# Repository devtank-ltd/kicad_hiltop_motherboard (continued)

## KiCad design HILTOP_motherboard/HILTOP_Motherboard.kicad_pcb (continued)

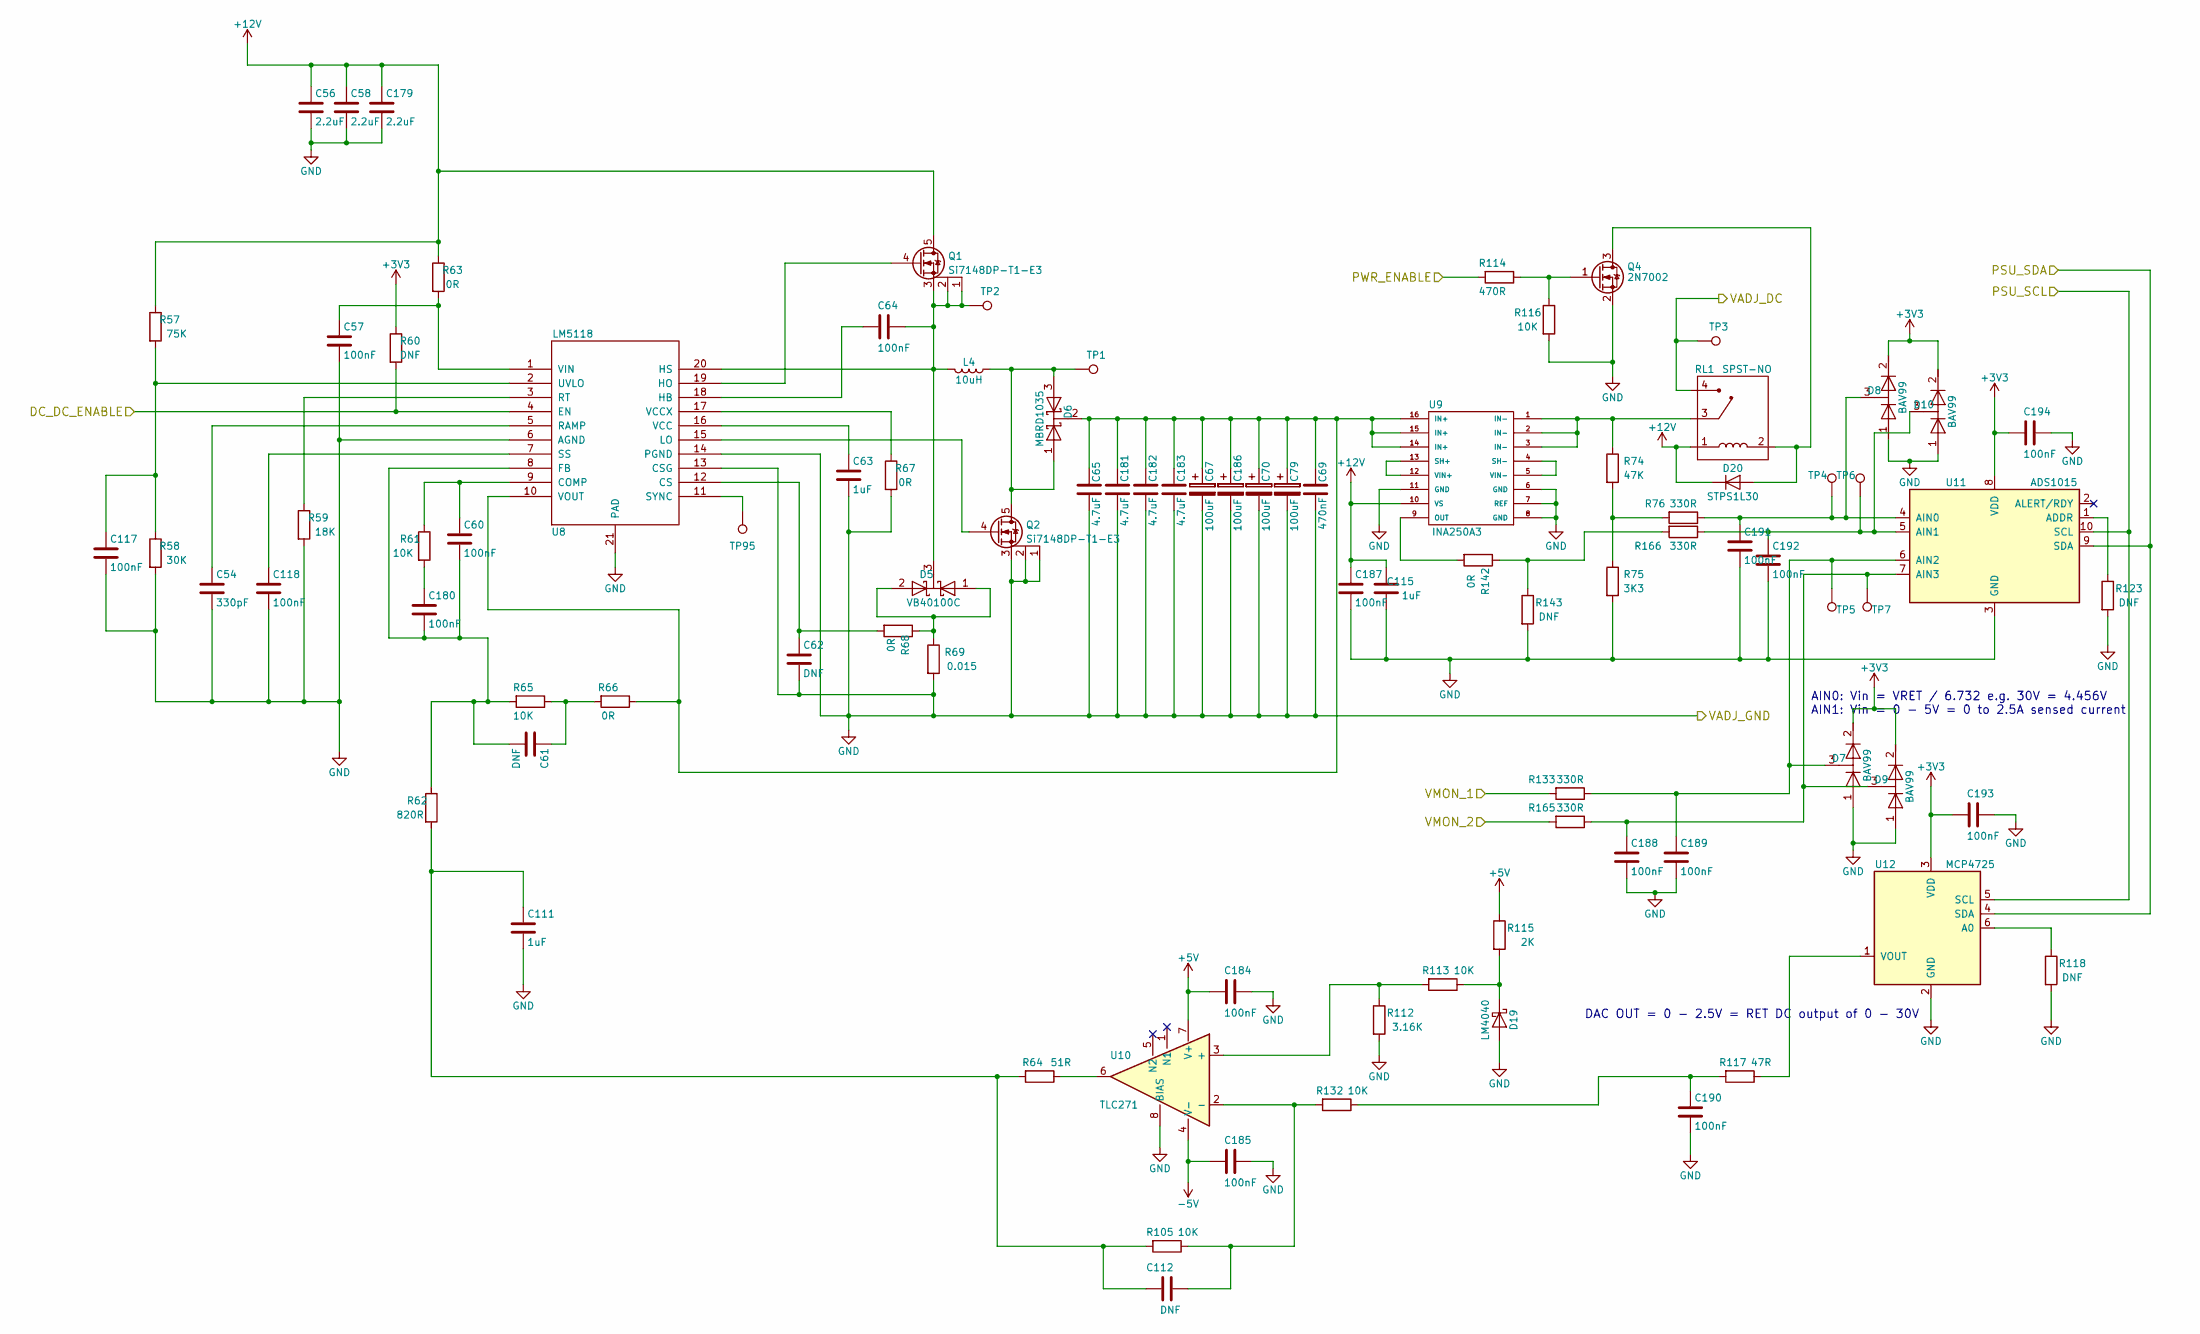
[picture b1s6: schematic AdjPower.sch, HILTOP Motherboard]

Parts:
C54: 330pF; C_0402_1005Metric
C56, C58, C179: 2.2uF; C_1206_3216Metric
C57, C60, C64, C117, C118, C180, C184, C185, C187, C188, C189, C190, C191, C192, C193, C194: 100nF; C_0603_1608Metric
C61, C62, C112: DNF; C_0603_1608Metric
C63, C111, C115: 1uF; C_0805_2012Metric
C65, C181, C182, C183: 4.7uF; C_1210_3225Metric
C67, C70, C79, C186: 100uF; CP_Elec_6.3x7.7
C69: 470nF; C_0805_2012Metric
D5: VB40100C; TO-263AB
D6: MBRD1035; DPAK
D7, D8, D9, D10: BAV99; SOT-23
D19: LM4040; SOT-23
D20: STPS1L30; D_SMB
L4: 10uH; Inductor_Coilcraft_SER2800
Q1, Q2: Si7148DP-T1-E3; PowerPAK_SO-8
Q4: 2N7002; SOT-23
R57: 75K; R_0603_1608Metric
R58: 30K; R_0603_1608Metric
R59: 18K; R_0603_1608Metric
R60, R118, R123, R143: DNF; R_0603_1608Metric
R61, R65, R105, R113, R116, R132: 10K; R_0603_1608Metric
R62: 820R; R_0603_1608Metric
R63: 0R; R_1206_3216Metric
R64: 51R; R_0603_1608Metric
R66, R67, R68, R142: 0R; R_0603_1608Metric
R69: 0.015; RL7520W_3008
R74: 47K; R_0603_1608Metric
R75: 3K3; R_0603_1608Metric
R76, R133, R165, R166: 330R; R_0603_1608Metric
R112: 3.16K; R_0603_1608Metric
R114: 470R; R_0603_1608Metric
R115: 2K; R_0603_1608Metric
R117: 47R; R_0603_1608Metric
RL1: SPST-NO; Relay_SPST_TE_PCH
TP1, TP2, TP3, TP4, TP5, TP6, TP7, TP95: TP; TestPoint_THTPad_D1.0mm_Drill0.5mm
U8: LM5118; HTSSOP-20-1EP_4.4x6.5mm_P0.65mm_ThermalPad
U9: INA250A3; TSSOP-16_4.4x5mm_P0.65mm
U10: TLC271; SOIC-8_3.9x4.9mm_P1.27mm
U11: ADS1015; TSSOP-10_3x3mm_P0.5mm
U12: MCP4725; SOT-23-6

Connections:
+3V3: C193.2, C194.2, D7.2 (K), D8.2 (K), D9.2 (K), D10.2 (K), R60.1, U11.8 (VDD), U12.3 (VDD); also elsewhere on the board
+12V: C56.1, C58.1, C115.2, C179.1, C187.1, D20.1 (K), Q1.5 (D), R57.1, R63.1, RL1.1, U9.10 (VS); also elsewhere on the board
-5V: C185.2, U10.4 (V-); also elsewhere on the board
/AdjPower/VADJ_DC: RL1.4, TP3.1; also elsewhere on the board
/AdjPower/VMON_1: R133.2; also elsewhere on the board
/AdjPower/VMON_2: R165.2; also elsewhere on the board
/DC_DC_ENABLE: R60.2, U8.4 (EN); also elsewhere on the board
/DC_OUT_ENABLE: R114.2; also elsewhere on the board
/I2C1_SCL: U11.10 (SCL), U12.5 (SCL); also elsewhere on the board
/I2C1_SDA: U11.9 (SDA), U12.4 (SDA); also elsewhere on the board
GND: C54.2, C56.2, C57.2, C58.2, C62.2, C63.2, C65.1, C67.2, C69.1, C70.2, C79.2, C111.2, C115.1, C117.2, C118.2, C179.2, C181.1, C182.1, C183.1, C184.1, C185.1, C186.2, C187.2, C188.2, C189.2, C190.2, C191.2, C192.2, C193.1, C194.1, D7.1 (A), D8.1 (A), D9.1 (A), D10.1 (A), D19.2 (A), Q2.1, Q2.2, Q2.3 (S), Q4.2 (S), R58.2, R59.2, R67.2, R69.2, R75.2, R112.2, R116.2, R118.2, R123.2, R143.2, U8.6 (AGND), U8.13 (CSG), U8.14 (PGND), U8.21 (PAD), U9.6 (GND), U9.7 (REF), U9.8 (GND), U9.11 (GND), U10.8 (BIAS), U11.3 (GND), U12.2 (GND); also elsewhere on the board
unnamed: C54.1, U8.5 (RAMP)
unnamed: C57.1, R63.2, U8.1 (VIN)
unnamed: C60.1, R61.1, U8.9 (COMP)
unnamed: C61.1, R65.1, R66.2
unnamed: C62.1, R68.2, U8.12 (CS)
unnamed: C63.1, U8.16 (VCC)
unnamed: C64.1, D5.3 (K), L4.2, Q1.1, Q1.2, Q1.3 (S), TP2.1, U8.20 (HS)
unnamed: C64.2, U8.18 (HB)
unnamed: C111.1, C112.1, R62.2, R64.2, R105.2
unnamed: C112.2, R105.1, R132.2, U10.2 (-)
unnamed: C117.1, R57.2, R58.1, U8.2 (UVLO)
unnamed: C118.1, U8.7 (SS)
unnamed: C180.1, R61.2
unnamed: C60.2, C61.2, C180.2, R62.1, R65.2, U8.8 (FB)
unnamed: C65.2, C67.1, C69.2, C70.1, C79.1, C181.2, C182.2, C183.2, C186.1, D6.2 (K), R66.1, U8.10 (VOUT), U9.14 (IN+), U9.15 (IN+), U9.16 (IN+)
unnamed: C188.1, D9.3 (common), R165.1, TP7.1, U11.7 (AIN3)
unnamed: C189.1, D7.3 (common), R133.1, TP5.1, U11.6 (AIN2)
unnamed: C190.1, R117.2, R132.1
unnamed: C191.1, D8.3 (common), R76.1, TP4.1, U11.4 (AIN0)
unnamed: C192.1, D10.3 (common), R166.1, TP6.1, U11.5 (AIN1)
unnamed: D5.1 (A), D5.2 (A), R68.1, R69.1
unnamed: D6.1 (A), D6.3 (A), L4.1, Q2.5 (D), TP1.1
unnamed: D19.1 (K), R113.1, R115.2
unnamed: D20.2 (A), Q4.3 (D), RL1.2
unnamed: Q1.4 (G), U8.19 (HO)
unnamed: Q2.4 (G), U8.15 (LO)
unnamed: Q4.1 (G), R114.1, R116.1
unnamed: R59.1, U8.3 (RT)
unnamed: R64.1, U10.6
unnamed: R67.1, U8.17 (VCCX)
unnamed: R74.1, RL1.3, U9.1 (IN-), U9.2 (IN-), U9.3 (IN-)
unnamed: R74.2, R75.1, R76.2
unnamed: R112.1, R113.2, U10.3 (+)
unnamed: R117.1, U12.1 (VOUT)
unnamed: R118.1, U12.6 (A0)
unnamed: R123.1, U11.1 (ADDR)
unnamed: R142.1, R143.1, R166.2
unnamed: R142.2, U9.9 (OUT)
unnamed: TP95.1, U8.11 (SYNC)
unnamed: U9.4 (SH-), U9.5 (VIN-)
unnamed: U9.12 (VIN+), U9.13 (SH+)

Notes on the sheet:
AIN0: Vin = VRET / 6.732 e.g. 30V = 4.456V AIN1: Vin = 0 - 5V = 0 to 2.5A sensed current
DAC OUT = 0 - 2.5V = RET DC output of 0 - 30V

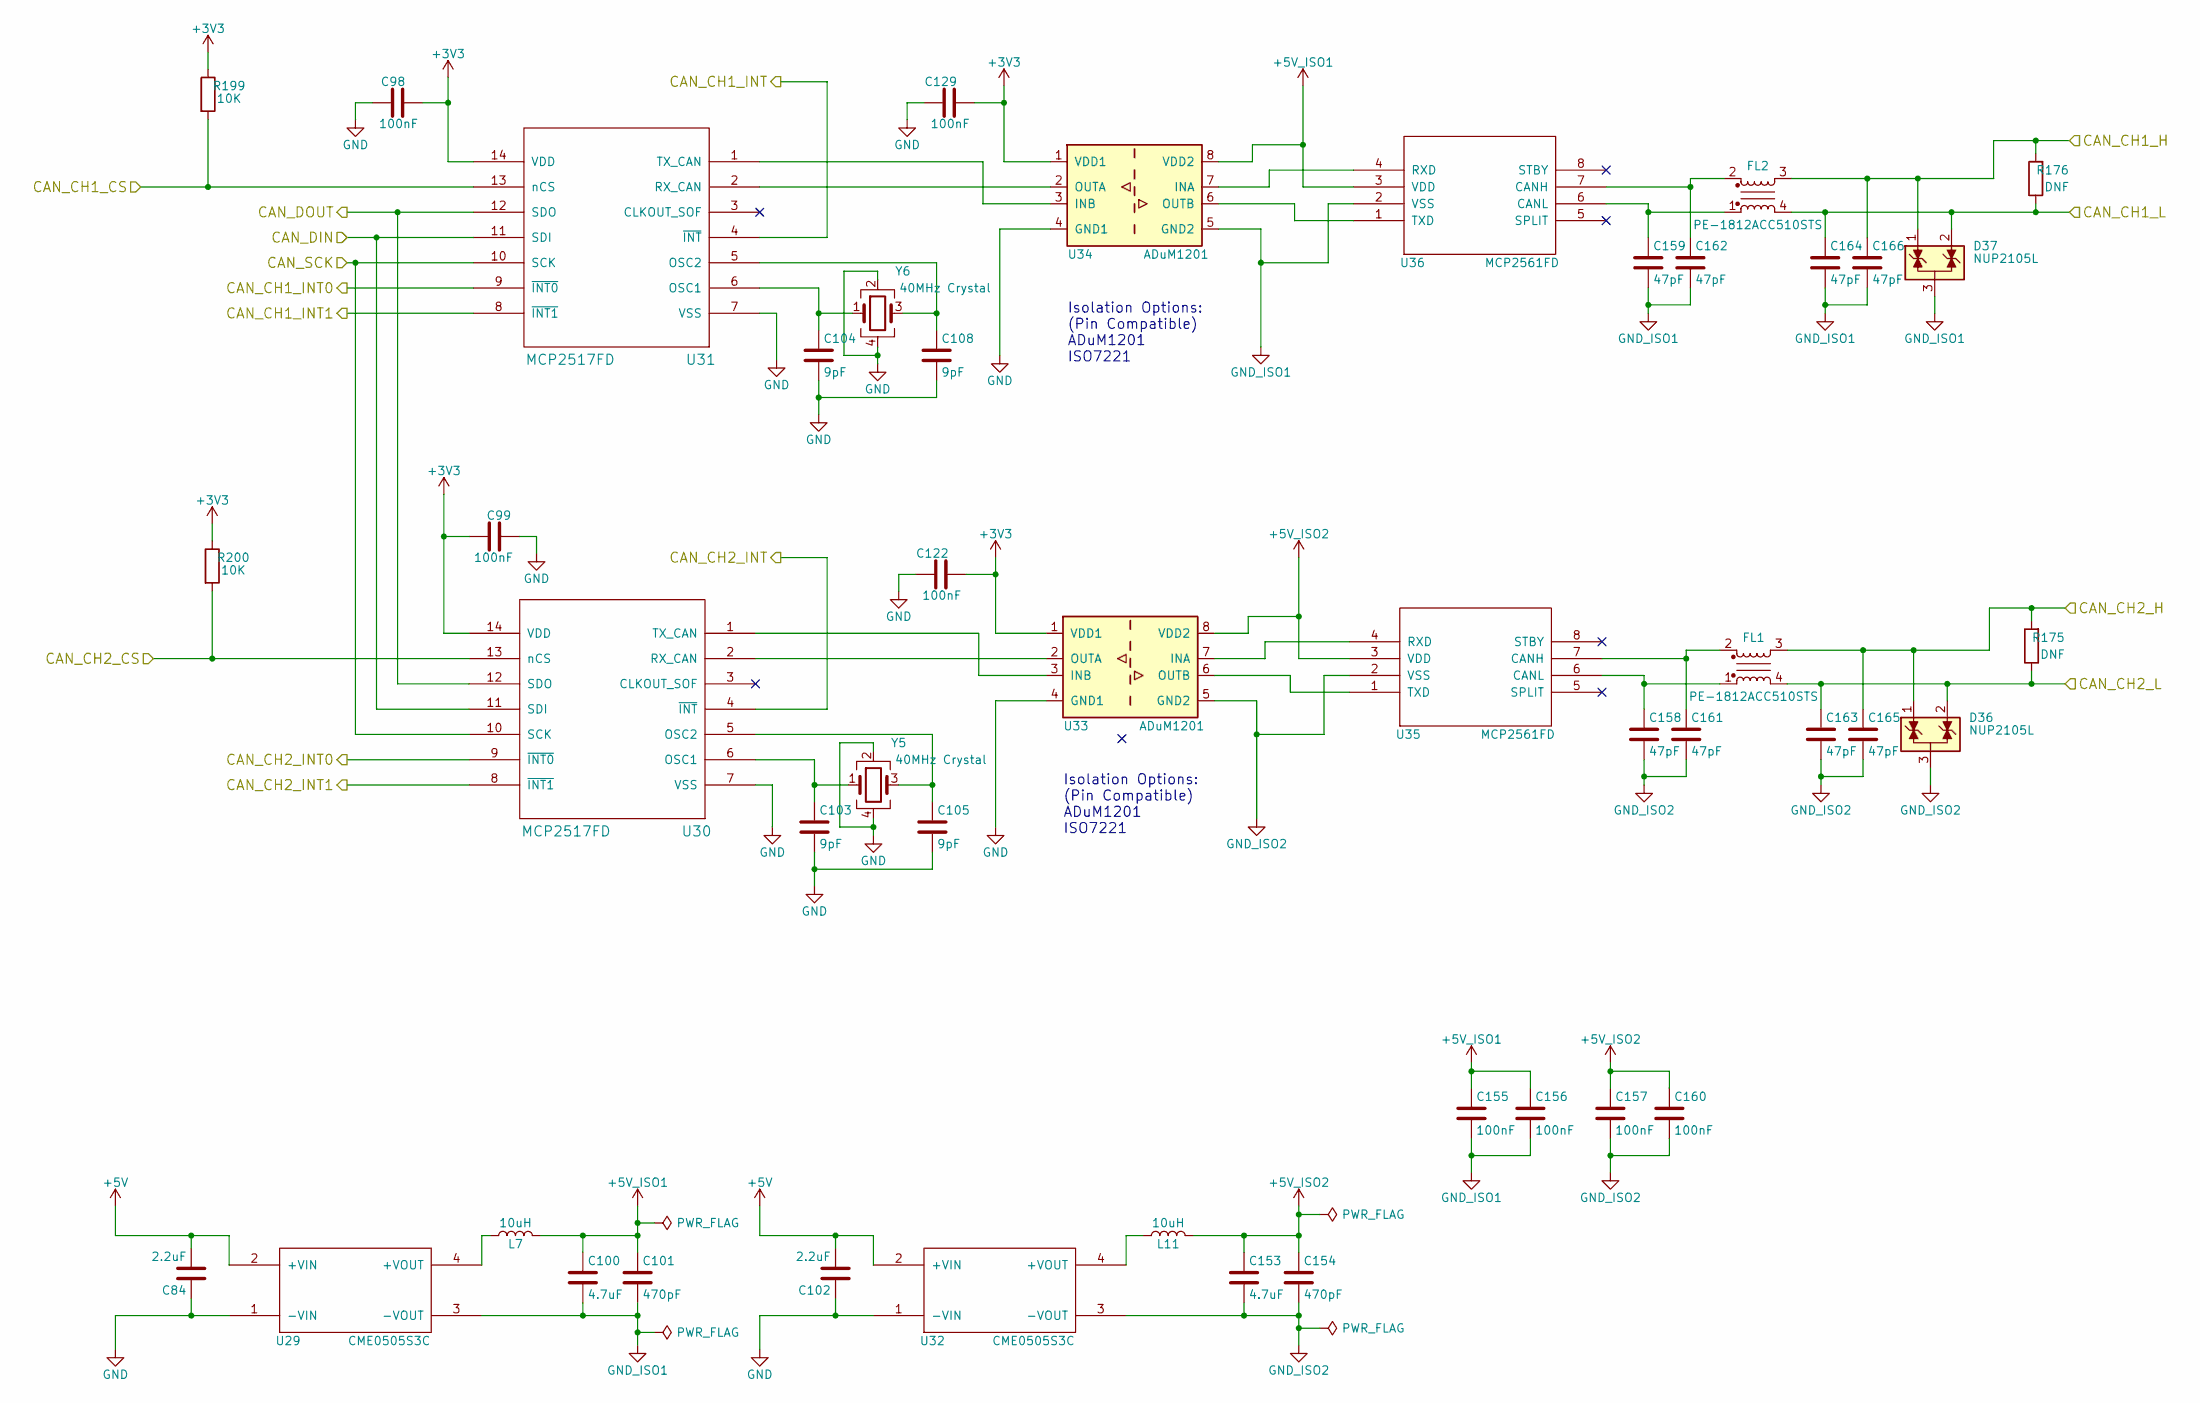
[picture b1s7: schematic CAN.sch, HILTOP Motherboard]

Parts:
C84, C102: 2.2uF; C_0805_2012Metric
C98, C99, C122, C129, C155, C156, C157, C160: 100nF; C_0603_1608Metric
C100, C153: 4.7uF; C_0805_2012Metric
C101, C154: 470pF; C_0603_1608Metric
C103, C104, C105, C108: 9pF; C_0603_1608Metric
C158, C159, C161, C162, C163, C164, C165, C166: 47pF; C_0603_1608Metric
D36, D37: NUP2105L; SOT-23
FL1, FL2: PE-1812ACC510STS; Inductor_PE-1812ACCXXXSTS
L7, L11: 10uH; Inductor_MuRata_82103C
R175, R176: DNF; R_0603_1608Metric
R199, R200: 10K; R_0603_1608Metric
U29, U32: CME0505S3C; CME_XXXX_S3C_PSU_MODULE
U30, U31: MCP2517FD; SOIC-14_3.9x8.7mm_P1.27mm
U33, U34: ADuM1201; SOIC-8_3.9x4.9mm_P1.27mm
U35, U36: MCP2561FD; SOIC-8_3.9x4.9mm_P1.27mm
Y5, Y6: 40MHz Crystal; Crystal_SMD_SeikoEpson_FA238V-4Pin_3.2x2.5mm

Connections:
+3V3: C98.2, C99.2, C122.2, C129.2, R199.1, R200.1, U30.14 (VDD), U31.14 (VDD), U33.1 (VDD1), U34.1 (VDD1); also elsewhere on the board
+5V_ISO1: C100.1, C101.1, C155.1, C156.1, L7.2, U34.8 (VDD2), U36.3 (VDD); also elsewhere on the board
+5V_ISO2: C153.1, C154.1, C157.1, C160.1, L11.2, U33.8 (VDD2), U35.3 (VDD); also elsewhere on the board
/CAN1_H: C166.1, D37.1 (K), FL2.3, R176.2; also elsewhere on the board
/CAN1_INT: U31.4 (~INT); also elsewhere on the board
/CAN1_L: C164.1, D37.2 (K), FL2.4, R176.1; also elsewhere on the board
/CAN2_H: C165.1, D36.1 (K), FL1.3, R175.2; also elsewhere on the board
/CAN2_INT: U30.4 (~INT); also elsewhere on the board
/CAN2_L: C163.1, D36.2 (K), FL1.4, R175.1; also elsewhere on the board
/CAN_CH1_CS: R199.2, U31.13 (nCS); also elsewhere on the board
/CAN_CH2_CS: R200.2, U30.13 (nCS); also elsewhere on the board
/SPI1_MISO: U30.12 (SDO), U31.12 (SDO); also elsewhere on the board
/SPI1_MOSI: U30.11 (SDI), U31.11 (SDI); also elsewhere on the board
/SPI1_SCLK: U30.10 (SCK), U31.10 (SCK); also elsewhere on the board
GND: C84.1, C98.1, C99.1, C102.1, C103.2, C104.2, C105.2, C108.2, C122.1, C129.1, U29.1 (-VIN), U30.7 (VSS), U31.7 (VSS), U32.1 (-VIN), U33.4 (GND1), U34.4 (GND1), Y5.2, Y5.4, Y6.2, Y6.4; also elsewhere on the board
GND_ISO1: C100.2, C101.2, C155.2, C156.2, C159.2, C162.2, C164.2, C166.2, D37.3 (A), U29.3 (-VOUT), U34.5 (GND2), U36.2 (VSS); also elsewhere on the board
GND_ISO2: C153.2, C154.2, C157.2, C158.2, C160.2, C161.2, C163.2, C165.2, D36.3 (A), U32.3 (-VOUT), U33.5 (GND2), U35.2 (VSS); also elsewhere on the board
unnamed: C103.1, U30.6 (OSC1), Y5.1
unnamed: C104.1, U31.6 (OSC1), Y6.1
unnamed: C105.1, U30.5 (OSC2), Y5.3
unnamed: C108.1, U31.5 (OSC2), Y6.3
unnamed: C158.1, FL1.1, U35.6 (CANL)
unnamed: C159.1, FL2.1, U36.6 (CANL)
unnamed: C161.1, FL1.2, U35.7 (CANH)
unnamed: C162.1, FL2.2, U36.7 (CANH)
unnamed: L7.1, U29.4 (+VOUT)
unnamed: L11.1, U32.4 (+VOUT)
unnamed: U30.1 (TX_CAN), U33.3 (INB)
unnamed: U30.2 (RX_CAN), U33.2 (OUTA)
unnamed: U31.1 (TX_CAN), U34.3 (INB)
unnamed: U31.2 (RX_CAN), U34.2 (OUTA)
unnamed: U33.6 (OUTB), U35.1 (TXD)
unnamed: U33.7 (INA), U35.4 (RXD)
unnamed: U34.6 (OUTB), U36.1 (TXD)
unnamed: U34.7 (INA), U36.4 (RXD)

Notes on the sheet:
Isolation Options: (Pin Compatible) ADuM1201 ISO7221

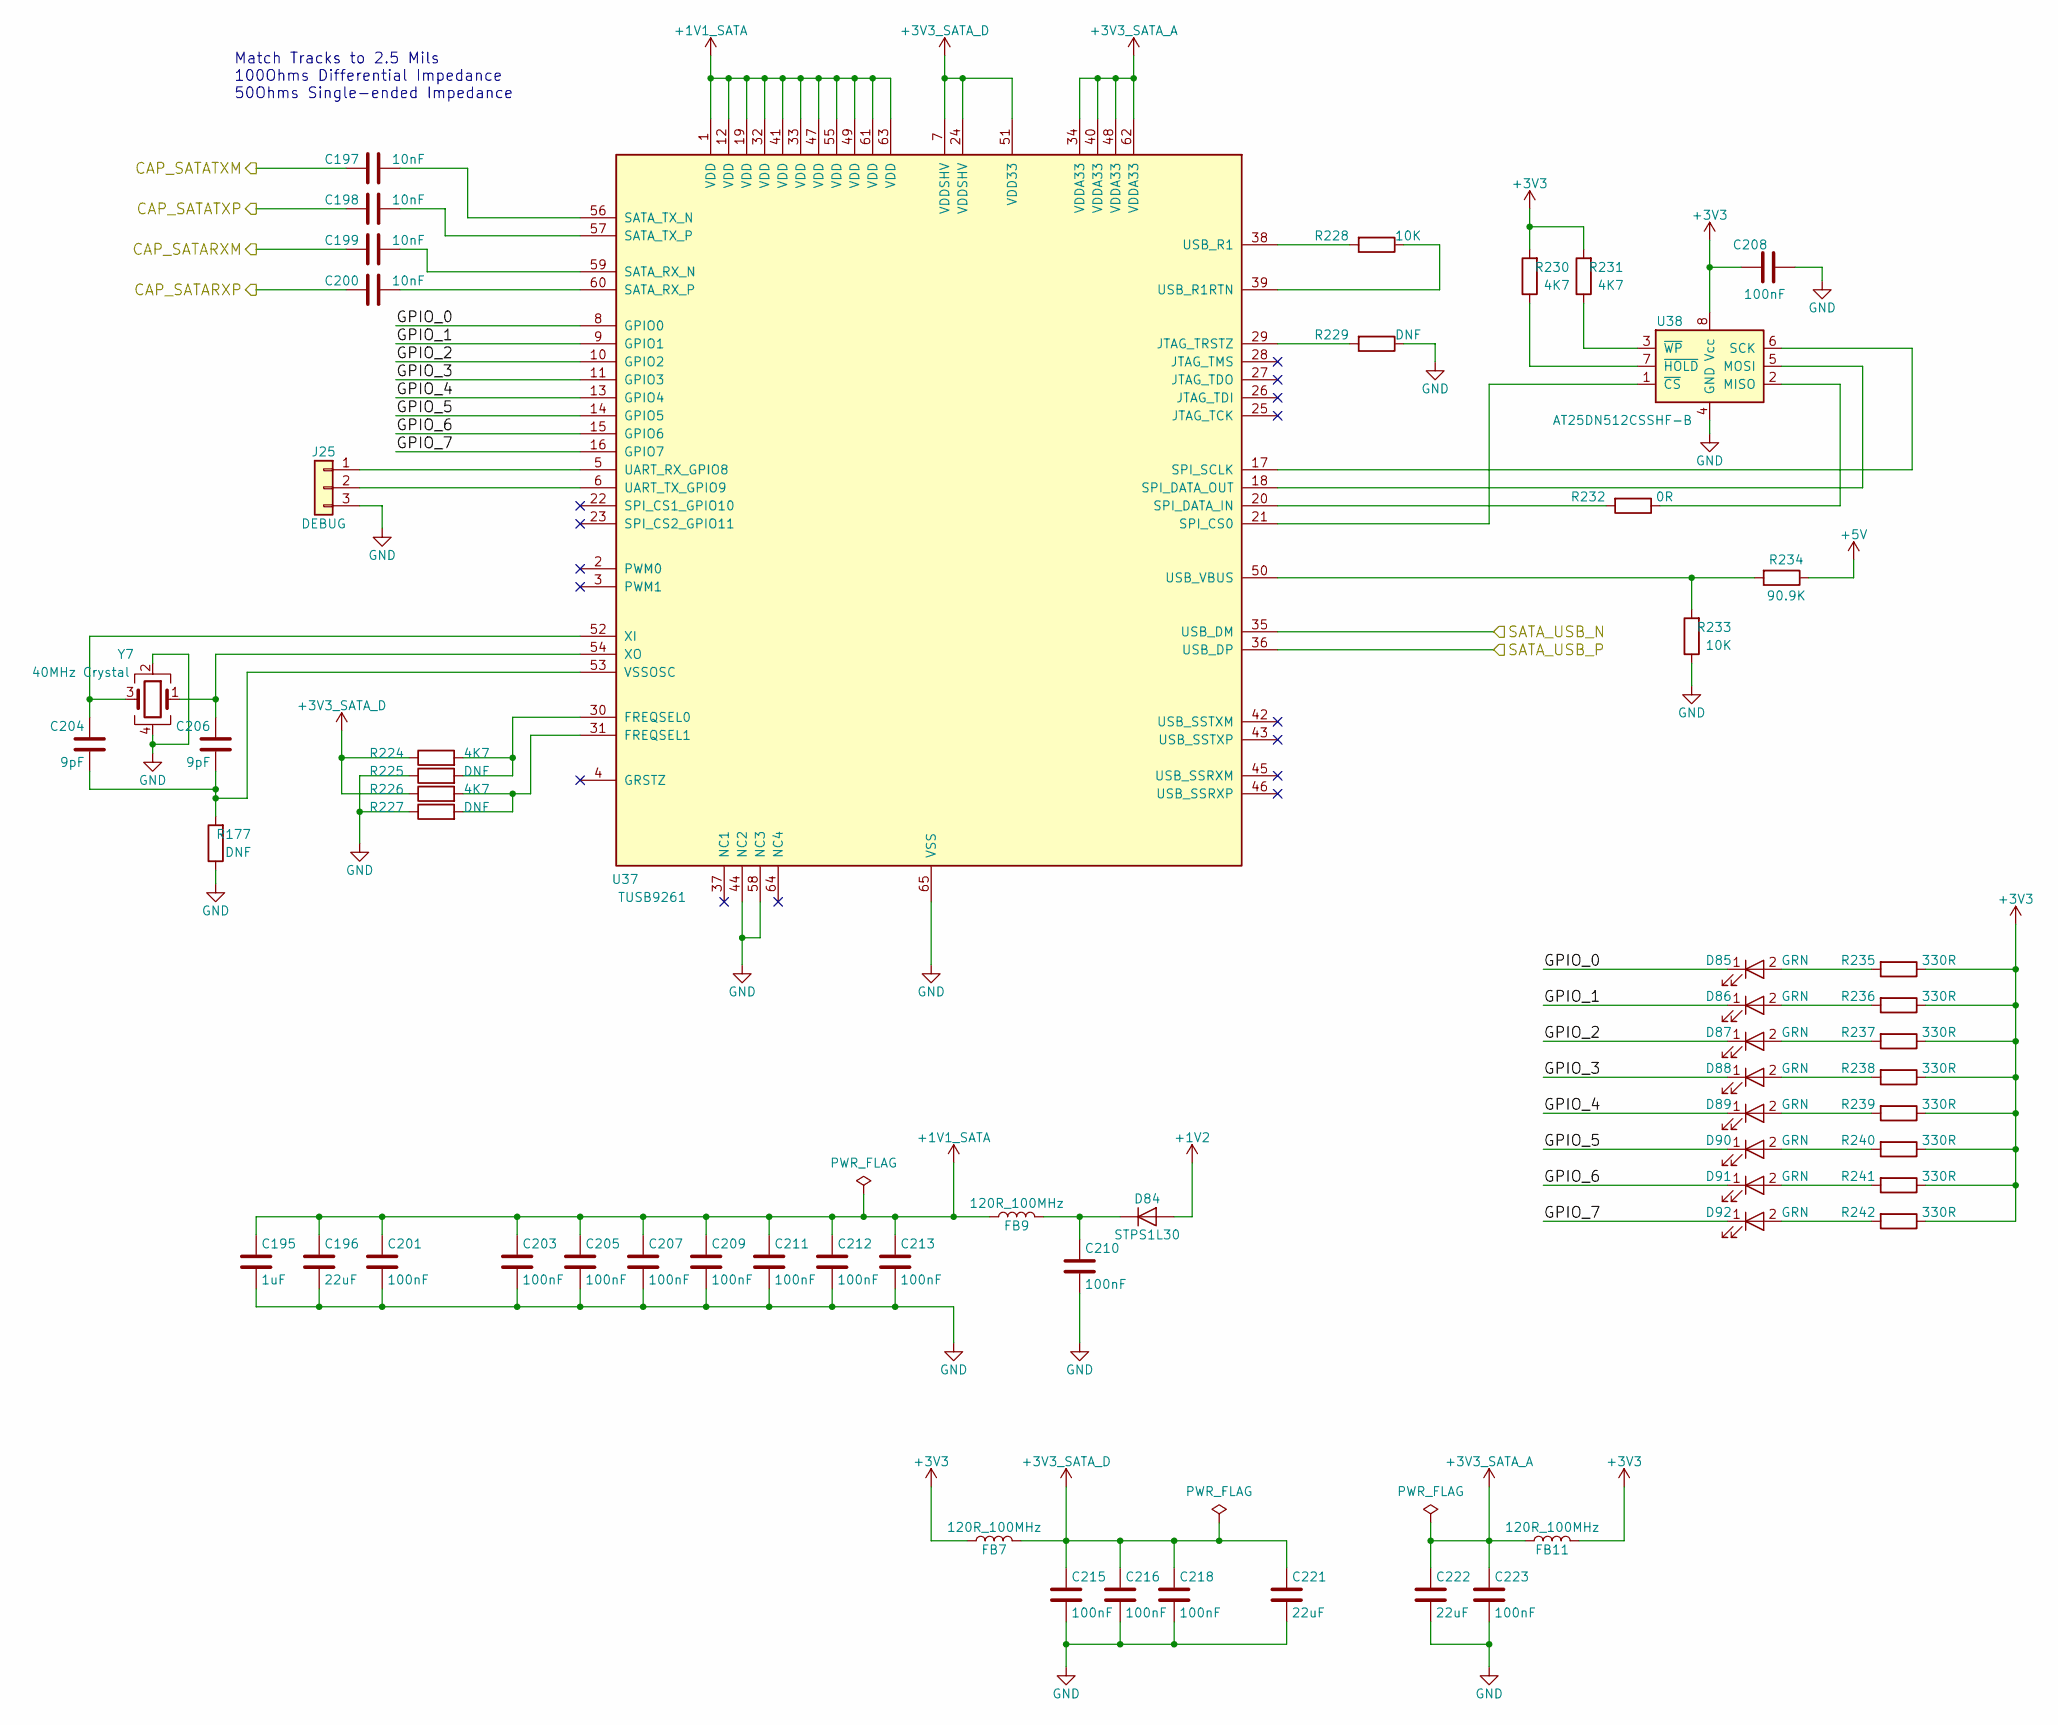
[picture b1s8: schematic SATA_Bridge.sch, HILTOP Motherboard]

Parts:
C195: 1uF; C_0603_1608Metric
C196, C221, C222: 22uF; C_1206_3216Metric
C197, C198, C199, C200: 10nF; C_0402_1005Metric
C201, C203, C205, C207, C208, C209, C210, C211, C212, C213, C215, C216, C218, C223: 100nF; C_0603_1608Metric
C204, C206: 9pF; C_0603_1608Metric
D84: STPS1L30; D_SMB
D85, D86, D87, D88, D89, D90, D91, D92: GRN; LED_0402_1005Metric
FB7, FB9, FB11: 120R_100MHz; R_0603_1608Metric
J25: DEBUG; PinHeader_1x03_P2.54mm_Vertical
R177, R225, R227, R229: DNF; R_0603_1608Metric
R224, R226, R230, R231: 4K7; R_0603_1608Metric
R228, R233: 10K; R_0603_1608Metric
R232: 0R; R_0603_1608Metric
R234: 90.9K; R_0603_1608Metric
R235, R236, R237, R238, R239, R240, R241, R242: 330R; R_0402_1005Metric
U37: TUSB9261; PQFP-64_7x7mm_P0.4mm_EP
U38: AT25DN512CSSHF-B; SOIC-8_3.9x4.9mm_P1.27mm
Y7: 40MHz Crystal; Crystal_SMD_SeikoEpson_FA238V-4Pin_3.2x2.5mm

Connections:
+1V1_SATA: C195.1, C196.1, C201.1, C203.1, C205.1, C207.1, C209.1, C211.1, C212.1, C213.1, FB9.1, U37.1 (VDD), U37.12 (VDD), U37.19 (VDD), U37.32 (VDD), U37.33 (VDD), U37.41 (VDD), U37.47 (VDD), U37.49 (VDD), U37.55 (VDD), U37.61 (VDD), U37.63 (VDD)
+1V2: D84.2 (A); also elsewhere on the board
+3V3: C208.1, FB7.1, FB11.2, R230.2, R231.2, R235.1, R236.1, R237.1, R238.1, R239.1, R240.1, R241.1, R242.1, U38.8 (Vcc); also elsewhere on the board
+3V3_SATA_A: C222.1, C223.1, FB11.1, U37.34 (VDDA33), U37.40 (VDDA33), U37.48 (VDDA33), U37.62 (VDDA33)
+3V3_SATA_D: C215.1, C216.1, C218.1, C221.1, FB7.2, R224.1, R226.1, U37.7 (VDDSHV), U37.24 (VDDSHV), U37.51 (VDD33)
/SATA_Bridge/CAP_SATARX_N: C199.2; also elsewhere on the board
/SATA_Bridge/CAP_SATARX_P: C200.2; also elsewhere on the board
/SATA_Bridge/CAP_SATATX_N: C198.2; also elsewhere on the board
/SATA_Bridge/CAP_SATATX_P: C197.2; also elsewhere on the board
/SATA_Bridge/GPIO_0: D85.1 (K), U37.8 (GPIO0)
/SATA_Bridge/GPIO_1: D86.1 (K), U37.9 (GPIO1)
/SATA_Bridge/GPIO_2: D87.1 (K), U37.10 (GPIO2)
/SATA_Bridge/GPIO_3: D88.1 (K), U37.11 (GPIO3)
/SATA_Bridge/GPIO_4: D89.1 (K), U37.13 (GPIO4)
/SATA_Bridge/GPIO_5: D90.1 (K), U37.14 (GPIO5)
/SATA_Bridge/GPIO_6: D91.1 (K), U37.15 (GPIO6)
/SATA_Bridge/GPIO_7: D92.1 (K), U37.16 (GPIO7)
/SATA_Bridge/RX_N: C199.1, U37.59 (SATA_RX_N)
/SATA_Bridge/RX_P: C200.1, U37.60 (SATA_RX_P)
/SATA_Bridge/TX_N: C197.1, U37.56 (SATA_TX_N)
/SATA_Bridge/TX_P: C198.1, U37.57 (SATA_TX_P)
/SATA_USB_N: U37.35 (USB_DM); also elsewhere on the board
/SATA_USB_P: U37.36 (USB_DP); also elsewhere on the board
GND: C195.2, C196.2, C201.2, C203.2, C205.2, C207.2, C208.2, C209.2, C210.2, C211.2, C212.2, C213.2, C215.2, C216.2, C218.2, C221.2, C222.2, C223.2, J25.3, R177.1, R225.1, R227.1, R229.1, R233.1, U37.44 (NC2), U37.58 (NC3), U37.65 (VSS), U38.4 (GND), Y7.2, Y7.4; also elsewhere on the board
unnamed: C204.1, U37.52 (XI), Y7.3
unnamed: C204.2, C206.2, R177.2, U37.53 (VSSOSC)
unnamed: C206.1, U37.54 (XO), Y7.1
unnamed: C210.1, D84.1 (K), FB9.2
unnamed: D85.2 (A), R235.2
unnamed: D86.2 (A), R236.2
unnamed: D87.2 (A), R237.2
unnamed: D88.2 (A), R238.2
unnamed: D89.2 (A), R239.2
unnamed: D90.2 (A), R240.2
unnamed: D91.2 (A), R241.2
unnamed: D92.2 (A), R242.2
unnamed: J25.1, U37.5 (UART_RX_GPIO8)
unnamed: J25.2, U37.6 (UART_TX_GPIO9)
unnamed: R224.2, R225.2, U37.30 (FREQSEL0)
unnamed: R226.2, R227.2, U37.31 (FREQSEL1)
unnamed: R228.1, U37.39 (USB_R1RTN)
unnamed: R228.2, U37.38 (USB_R1)
unnamed: R229.2, U37.29 (JTAG_TRSTZ)
unnamed: R230.1, U38.7 (~HOLD)
unnamed: R231.1, U38.3 (~WP)
unnamed: R232.1, U38.2 (MISO)
unnamed: R232.2, U37.20 (SPI_DATA_IN)
unnamed: R233.2, R234.2, U37.50 (USB_VBUS)
unnamed: U37.17 (SPI_SCLK), U38.6 (SCK)
unnamed: U37.18 (SPI_DATA_OUT), U38.5 (MOSI)
unnamed: U37.21 (SPI_CS0), U38.1 (~CS)

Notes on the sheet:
Match Tracks to 2.5 Mils 100Ohms Differential Impedance 50Ohms Single-ended Impedance

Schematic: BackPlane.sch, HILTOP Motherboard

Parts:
J24: HILTOP_PCIE-64_CONN; PCIE-064-02-X-D-TH

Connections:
/BACKPLANE_USB_N: J24.B2 (USB_N); also elsewhere on the board
/BACKPLANE_USB_P: J24.B1 (USB_P); also elsewhere on the board
/BCK_SHUTDOWN: J24.B5 (SHUTDOWN); also elsewhere on the board
/I2C0_SCL: J24.B24 (I2C0_SCL/BCM1); also elsewhere on the board
/I2C0_SDA: J24.B23 (I2C0_SDA/BCM0); also elsewhere on the board
/I2C1_SCL: J24.B27 (I2C1_SCL/BCM3); also elsewhere on the board
/I2C1_SDA: J24.B26 (I2C1_SDA/BCM2); also elsewhere on the board
/PORT1_SEL: J24.A5 (PSEL/BCM38); also elsewhere on the board
/PORT2_SEL: J24.A6 (PSEL/BCM39); also elsewhere on the board
/PORT3_SEL: J24.A7 (PSEL/BCM40); also elsewhere on the board
/PORT4_SEL: J24.A8 (PSEL/BCM41); also elsewhere on the board
/PORT5_SEL: J24.A9 (PSEL/BCM42); also elsewhere on the board
/PORT6_SEL: J24.A10 (PSEL/BCM43); also elsewhere on the board
/PR_GPIO22: J24.B10 (GPIO1/BCM22); also elsewhere on the board
/PR_GPIO23: J24.B11 (GPIO2/BCM23); also elsewhere on the board
/PR_GPIO24: J24.B12 (GPIO3/BCM24); also elsewhere on the board
/PR_GPIO25: J24.B13 (GPIO4/BCM25); also elsewhere on the board
/PR_GPIO26: J24.B14 (GPIO5/BCM26); also elsewhere on the board
/PR_GPIO27: J24.B16 (GPIO6/BCM27); also elsewhere on the board
/PR_GPIO28: J24.B17 (GPIO7/BCM28); also elsewhere on the board
/PR_GPIO34: J24.B18 (GPIO8/BCM34); also elsewhere on the board
/PR_GPIO35: J24.B20 (GPIO9/BCM35); also elsewhere on the board
/PR_GPIO36: J24.B21 (GPIO10/BCM36); also elsewhere on the board
/SPI0_CS0: J24.A20 (SPIO_CS0/BCM8); also elsewhere on the board
/SPI0_CS1: J24.A21 (SPI0_CS1/BCM7); also elsewhere on the board
/SPI0_MISO: J24.A18 (SPIO_MISO/BCM9); also elsewhere on the board
/SPI0_MOSI: J24.A17 (SPIO_MOSI/BCM10); also elsewhere on the board
/SPI0_SCLK: J24.A19 (SPIO_CLK/BCM11); also elsewhere on the board
/SPI1_CS0: J24.A26 (SPI1_CS0/BCM18); also elsewhere on the board
/SPI1_CS1_CAM_IO0: J24.A27 (SPI1_CS1/BCM17); also elsewhere on the board
/SPI1_CS2_CAM_IO1: J24.B29 (GPIO11); also elsewhere on the board
/SPI1_MISO: J24.A24 (SPI1_MISO/BCM19); also elsewhere on the board
/SPI1_MOSI: J24.A23 (SPI1_MOSI/BCM20); also elsewhere on the board
/SPI1_SCLK: J24.A25 (SPI1_CLK/BCM21); also elsewhere on the board
/SYS_CLK1: J24.A2 (SYS_CLK/BCM5); also elsewhere on the board
/SYS_PWM0: J24.B7 (PWM0/BCM12); also elsewhere on the board
/SYS_PWM1: J24.B8 (PWM1/BCM13); also elsewhere on the board
/SYS_TRIG: J24.A3 (SYS_TRIG/BCM6); also elsewhere on the board
/~MASTER_RESET: J24.B4 (RESET); also elsewhere on the board
GND: J24.A1 (GND), J24.A4 (GND), J24.A11 (GND), J24.A16 (GND), J24.A22 (GND), J24.A28 (GND), J24.A32 (GND), J24.B3 (GND), J24.B6 (GND), J24.B9 (GND), J24.B15 (GND), J24.B19 (GND), J24.B22 (GND), J24.B25 (GND), J24.B28 (GND), J24.B32 (GND); also elsewhere on the board

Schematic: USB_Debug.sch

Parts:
C217, C224: 4.7uF; C_0805_2012Metric
C219, C225: 100nF; C_0603_1608Metric
D32, D33: GRN; LED_0402_1005Metric
R201, R203, R208, R209: 0R; R_0603_1608Metric
R202: DNF; R_0603_1608Metric
R204, R205: 330R; R_0603_1608Metric
U40: SP3003-02XJ; SC70-5
U41: CP2102N-A01-GQFN24; QFN-24-1EP_4x4mm_P0.5mm_EP2.6x2.6mm_ThermalVias

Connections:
+3V3: C217.1, C219.1, C224.1, C225.1, D32.2 (A), D33.2 (A), R202.2, U41.5 (VIO), U41.6 (VDD), U41.7 (REGIN); also elsewhere on the board
/DEBUG_RX: R209.1; also elsewhere on the board
/DEBUG_TX: R208.1; also elsewhere on the board
/USB_Debug/USB_BUS_PWR: R203.2; also elsewhere on the board
/USB_Debug/USB_N: U40.4 (IO2), U41.4 (D-); also elsewhere on the board
/USB_Debug/USB_P: U40.5 (IO1), U41.3 (D+); also elsewhere on the board
/~MASTER_RESET: R201.2; also elsewhere on the board
GND: C217.2, C219.2, C224.2, C225.2, U40.2 (GND), U41.2 (GND), U41.25 (GND); also elsewhere on the board
unnamed: D32.1 (K), R204.1
unnamed: D33.1 (K), R205.1
unnamed: R201.1, R202.1, U41.9 (~RSTb)
unnamed: R203.1, U41.8 (VBUS)
unnamed: R204.2, U41.13 (GPIO.1)
unnamed: R205.2, U41.14 (GPIO.0)
unnamed: R208.2, U41.20 (RXD)
unnamed: R209.2, U41.21 (TXD)

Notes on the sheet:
RXT
TXT

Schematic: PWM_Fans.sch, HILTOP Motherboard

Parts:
C237, C238: DNF; C_0603_1608Metric
Q5, Q6, Q7: ZXMN6A07F; SOT-23
Q8: SSM3J328R; SOT-23
R159, R184, R185, R217, R218: 10K; R_0603_1608Metric
R215, R216: 470R; R_0603_1608Metric
R219, R220: DNF; R_0603_1608Metric

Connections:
+12V: C237.1, Q8.2 (S), R184.1; also elsewhere on the board
/PWM_Fans/12V_SW_LOAD: C238.2, Q8.3 (D); also elsewhere on the board
/PWM_Fans/FAN1_OUT: Q5.3 (D), R219.2; also elsewhere on the board
/PWM_Fans/FAN2_OUT: Q6.3 (D), R220.2; also elsewhere on the board
/SYS_FAN_DC: Q7.1 (G), R159.1; also elsewhere on the board
/SYS_FAN_PWM: R215.2, R216.2; also elsewhere on the board
GND: Q5.2 (S), Q6.2 (S), Q7.2 (S), R159.2, R217.2, R218.2; also elsewhere on the board
unnamed: C237.2, C238.1, Q8.1 (G), R184.2, R185.1
unnamed: Q5.1 (G), R215.1, R217.1
unnamed: Q6.1 (G), R216.1, R218.1
unnamed: Q7.3 (D), R185.2

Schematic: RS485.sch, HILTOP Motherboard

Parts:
C43, C46: 470pF; C_0603_1608Metric
C44, C78: 2.2uF; C_0805_2012Metric
C45, C76: 4.7uF; C_0805_2012Metric
C80, C81, C82, C83, C226, C228, C230, C231, C232, C233, C234, C235: 100nF; C_0603_1608Metric
C227, C229: 1uF; C_0603_1608Metric
FB6, FB10: 120R_100MHz; R_0603_1608Metric
L5, L6: 15uH; Inductor_MuRata_82103C
R81, R221, R222, R244: 10K; R_0603_1608Metric
R223: 0R; R_0603_1608Metric
R243: DNF; R_0603_1608Metric
U13, U17: AM1S-0505SZ; CME_XXXX_S3C_PSU_MODULE
U15, U16: ISO3080; SOIC-16W_7.5x10.3mm_P1.27mm
U18, U19, U20, U21: USB6B1; SOIC-8_3.9x4.9mm_P1.27mm
U43, U44: MAX3107; SSOP-24_5.3x8.2mm_P0.65mm
Y8, Y9: 3.6864MHz Crystal; Crystal_SMD_SeikoEpson_MA505-2Pin_12.7x5.1mm

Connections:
+2V5: FB6.1, FB10.1; also elsewhere on the board
+3V3: C80.2, C81.2, C226.2, C228.2, C232.1, C233.1, C234.1, C235.1, R221.1, R222.1, R243.1, U15.1 (VCC1), U16.1 (VCC1), U43.5 (~I2C/~SPI), U43.6 (LDOEN), U43.13 (VL), U43.23 (VEXT), U44.5 (~I2C/~SPI), U44.6 (LDOEN), U44.13 (VL), U44.23 (VEXT); also elsewhere on the board
/A1: U18.6 (I/O1); also elsewhere on the board
/A2: U20.6 (I/O1); also elsewhere on the board
/B1: U18.7 (I/O2); also elsewhere on the board
/B2: U20.7 (I/O2); also elsewhere on the board
/SPI0_MISO: U43.7 (DOUT/SDA), U44.7 (DOUT/SDA); also elsewhere on the board
/SPI0_MOSI: U43.10 (DIN/A1), U44.10 (DIN/A1); also elsewhere on the board
/SPI0_SCLK: U43.8 (SCLK/SCL), U44.8 (SCLK/SCL); also elsewhere on the board
/UART_CH1_CS: R221.2, U43.9 (~CS/~A0); also elsewhere on the board
/UART_CH1_IRQ: U43.11 (~IRQ); also elsewhere on the board
/UART_CH2_CS: R222.2, U44.9 (~CS/~A0); also elsewhere on the board
/UART_CH2_IRQ: U44.11 (~IRQ); also elsewhere on the board
/Y1: U19.7 (I/O2); also elsewhere on the board
/Y2: U21.7 (I/O2); also elsewhere on the board
/Z1: U19.6 (I/O1); also elsewhere on the board
/Z2: U21.6 (I/O1); also elsewhere on the board
/~MASTER_RESET: R223.2; also elsewhere on the board
GND: C44.1, C78.1, C80.1, C81.1, C226.1, C227.1, C228.1, C229.1, C230.1, C231.1, C232.2, C233.2, C234.2, C235.2, R81.2, R244.2, U13.1 (-VIN), U15.2 (GND1), U15.4 (~RE), U15.7 (GND1), U15.8 (GND1), U16.2 (GND1), U16.4 (~RE), U16.7 (GND1), U16.8 (GND1), U17.1 (-VIN), U43.2 (AGND), U43.14 (DGND), U44.2 (AGND), U44.14 (DGND); also elsewhere on the board
GND_ISO3: C43.2, C76.2, C82.2, U13.3 (-VOUT), U15.9 (GND2), U15.10 (GND2), U15.15 (GND2), U18.4 (GND), U18.8 (GND), U19.4 (GND), U19.8 (GND); also elsewhere on the board
GND_ISO4: C45.2, C46.2, C83.2, U16.9 (GND2), U16.10 (GND2), U16.15 (GND2), U17.3 (-VOUT), U20.4 (GND), U20.8 (GND), U21.4 (GND), U21.8 (GND); also elsewhere on the board
unnamed: C227.2, U43.4 (V18)
unnamed: C229.2, U44.4 (V18)
unnamed: C230.2, FB6.2, U43.3 (VA)
unnamed: C231.2, FB10.2, U44.3 (VA)
unnamed: R81.1, U15.5 (DE), U43.20 (~RTS~/CLKOUT)
unnamed: R223.1, R243.2, U43.12 (~RST), U44.12 (~RST)
unnamed: R244.1, U16.5 (DE), U44.20 (~RTS~/CLKOUT)
unnamed: U15.3 (R), U43.21 (RX)
unnamed: U15.6 (D), U43.22 (TX)
unnamed: U15.11 (Y), U19.3 (I/O2)
unnamed: U15.12 (Z), U19.2 (I/O1)
unnamed: U15.13 (B), U18.3 (I/O2)
unnamed: U15.14 (A), U18.2 (I/O1)
unnamed: U16.3 (R), U44.21 (RX)
unnamed: U16.6 (D), U44.22 (TX)
unnamed: U16.11 (Y), U21.3 (I/O2)
unnamed: U16.12 (Z), U21.2 (I/O1)
unnamed: U16.13 (B), U20.3 (I/O2)
unnamed: U16.14 (A), U20.2 (I/O1)
unnamed: U43.1 (XIN), Y8.1
unnamed: U43.24 (XOUT), Y8.2
unnamed: U44.1 (XIN), Y9.1
unnamed: U44.24 (XOUT), Y9.2

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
